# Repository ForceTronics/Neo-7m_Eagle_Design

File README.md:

# Neo-7m_Eagle_Design
Reference or evaluation PCB design for the ublox Neo-7m GNSS / GPS module

Free to use and modify at your own risk

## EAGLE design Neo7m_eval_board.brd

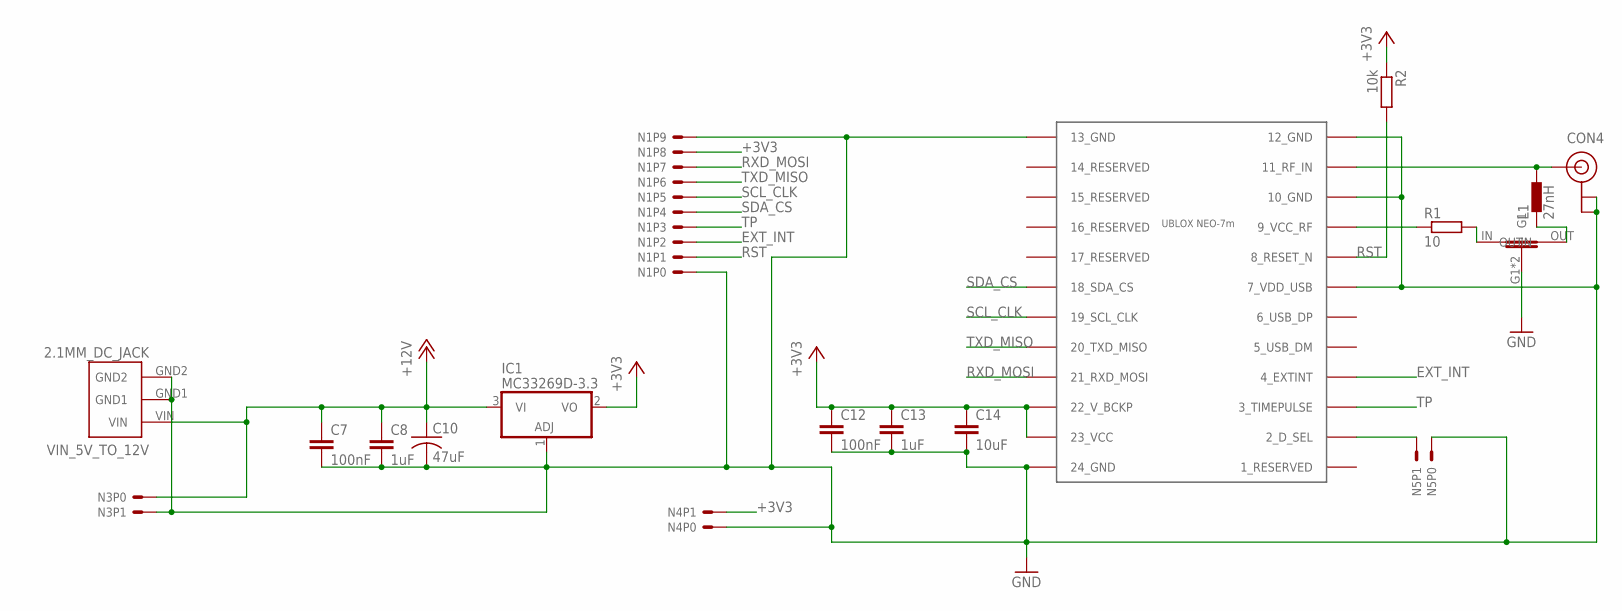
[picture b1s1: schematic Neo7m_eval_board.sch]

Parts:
C7, C12: 100nF; C1206
C8, C13: 1uF; C1206
C10: 47uF; 47UF_AL_SMD
C14: 10uF; C1206
CON4: U.FL
IC1: MC33269D-3.3; DPACK
L1: 27nH; 0402
N1: 10PINHEADER
N3, N4, N5: 2PINHEADER
R1: 10; R1206
R2: 10k; R1206
U$1: FEEDTHRU_CAP_1206
U$4: UBLOX_NEO7M
VIN_5V_TO_12V: 2.1MM_DC_JACK

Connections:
+3V3: C12.1, C13.1, C14.1, IC1.2 (VO), N1.P8, N4.P1, R2.1, U$4.22_V_BCKP, U$4.23_VCC
+12V: C7.1, C8.1, C10.P$1 (1), IC1.3 (VI), N3.P0, VIN_5V_TO_12V.VIN
EXT_INT: N1.P2, U$4.4_EXTINT
GND: C7.2, C8.2, C10.P$2 (2), C12.2, C13.2, C14.2, CON4.P$1 (GND), CON4.P$2 (GND), IC1.1 (ADJ), N1.P0, N1.P9, N3.P1, N4.P0, N5.P0, U$1.G1, U$1.G2 (G1), U$4.7_VDD_USB, U$4.10_GND, U$4.12_GND, U$4.13_GND, U$4.24_GND, VIN_5V_TO_12V.GND1, VIN_5V_TO_12V.GND2
unnamed: R1.2, U$1.IN
unnamed: R1.1, U$4.9_VCC_RF
unnamed: L1.1, U$1.OUT
unnamed: N5.P1, U$4.2_D_SEL
unnamed: CON4.P$3 (SIGNAL), L1.2, U$4.11_RF_IN
RST: N1.P1, R2.2, U$4.8_RESET_N
RXD_MOSI: N1.P7, U$4.21_RXD_MOSI
SCL_CLK: N1.P5, U$4.19_SCL_CLK
SDA_CS: N1.P4, U$4.18_SDA_CS
TP: N1.P3, U$4.3_TIMEPULSE
TXD_MISO: N1.P6, U$4.20_TXD_MISO

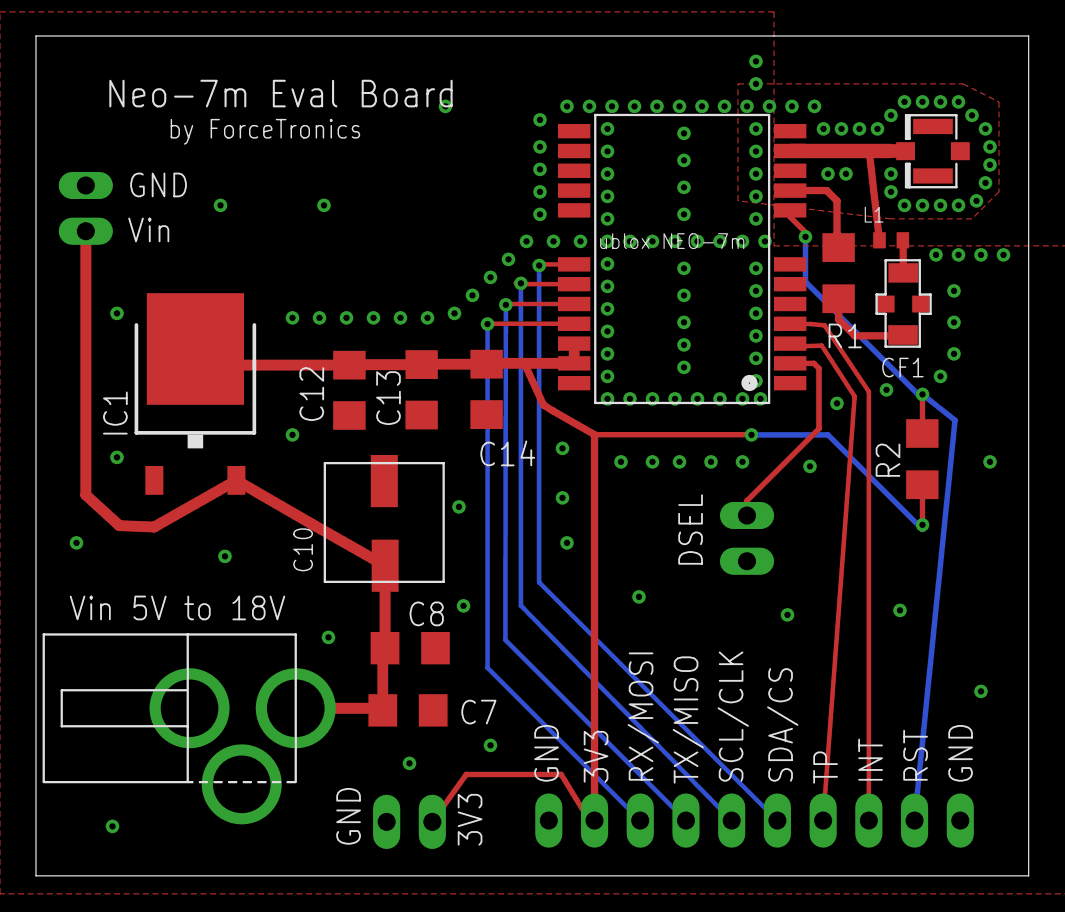
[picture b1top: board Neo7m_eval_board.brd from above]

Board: 2 copper layers, 55.1 x 46.7 mm, 18 parts (0 on the bottom side), 15 nets.

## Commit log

2017-08-26 Board file
2017-08-26 Schematic file
2017-09-06 Update, connected both DC jack ground connections to ground

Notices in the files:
parts and their libraries:
SparkFun-Connectors: Licensing: Creative Commons ShareAlike 4.0 International - https://creativecommons.org/licenses/by-sa/4.0
